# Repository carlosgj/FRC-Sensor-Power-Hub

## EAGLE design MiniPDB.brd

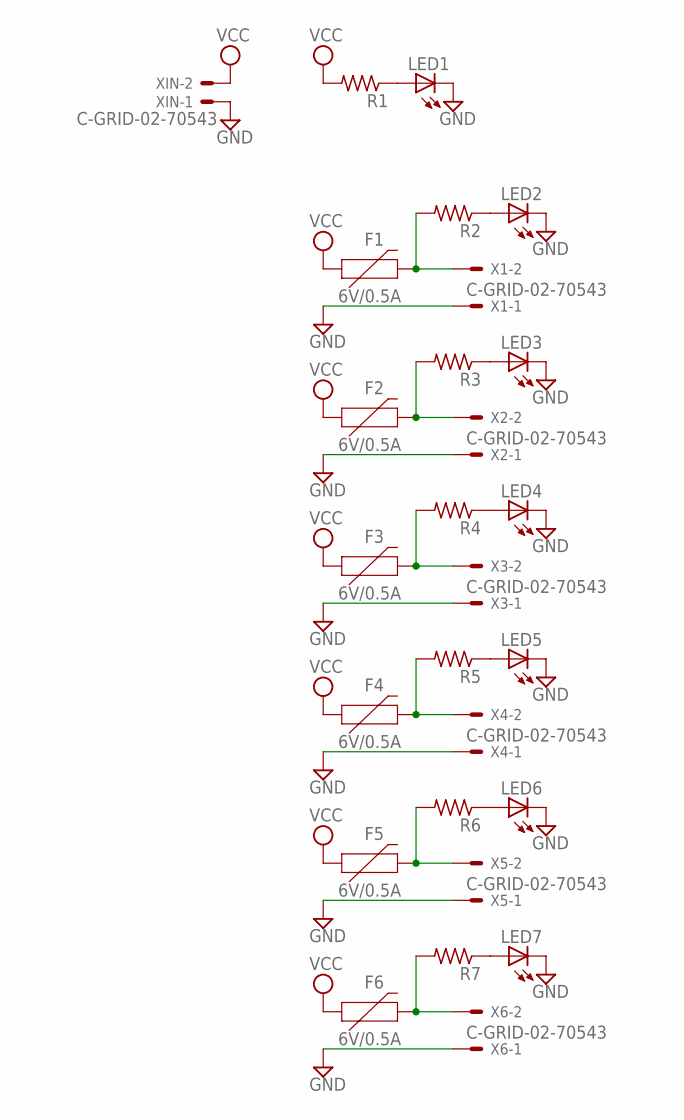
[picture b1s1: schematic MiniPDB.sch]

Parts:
F1, F2, F3, F4, F5, F6: 6V/0.5A; 1206
LED1, LED2, LED3, LED4, LED5, LED6, LED7: LEDCHIPLED_1206; CHIPLED_1206
R1, R2, R3, R4, R5, R6, R7: R-US_R1206; R1206
X1, X2, X3, X4, X5, X6: C-GRID-02-70543; 70543-02
XIN: C-GRID-02-70543; 70543-02

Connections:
GND: LED1.C, LED2.C, LED3.C, LED4.C, LED5.C, LED6.C, LED7.C, X1.1, X2.1, X3.1, X4.1, X5.1, X6.1, XIN.1
unnamed: F1.2, R2.2, X1.2
unnamed: LED2.A, R2.1
unnamed: LED1.A, R1.1
unnamed: F2.2, R3.2, X2.2
unnamed: LED3.A, R3.1
unnamed: F3.2, R4.2, X3.2
unnamed: LED4.A, R4.1
unnamed: F4.2, R5.2, X4.2
unnamed: LED5.A, R5.1
unnamed: F5.2, R6.2, X5.2
unnamed: LED6.A, R6.1
unnamed: F6.2, R7.2, X6.2
unnamed: LED7.A, R7.1
VCC: F1.1, F2.1, F3.1, F4.1, F5.1, F6.1, R1.2, XIN.2

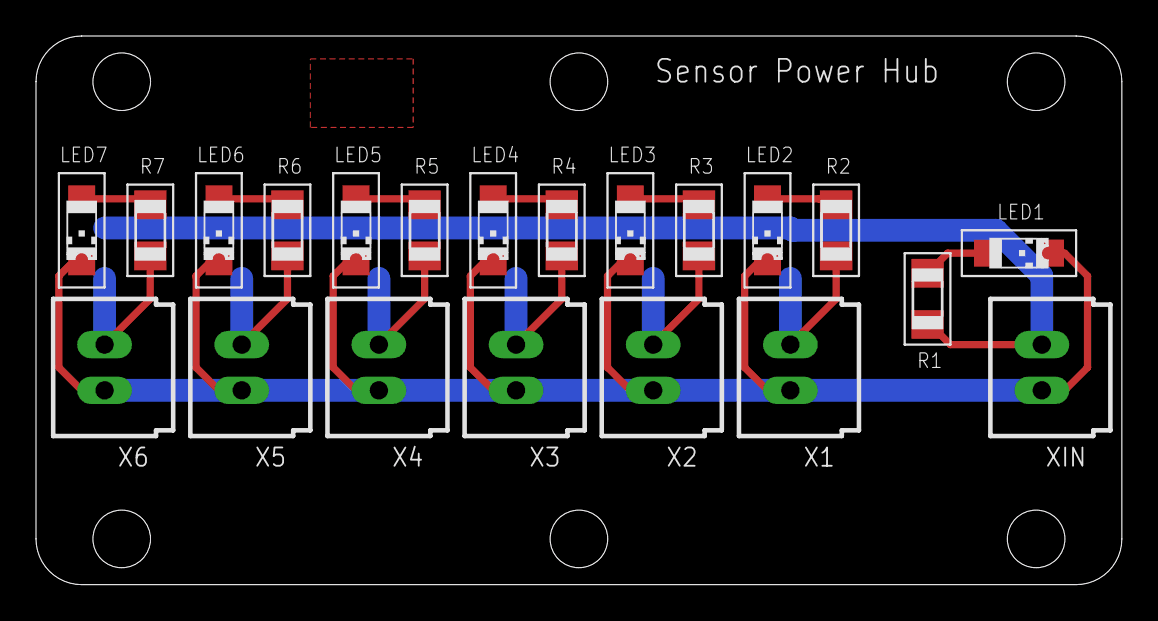
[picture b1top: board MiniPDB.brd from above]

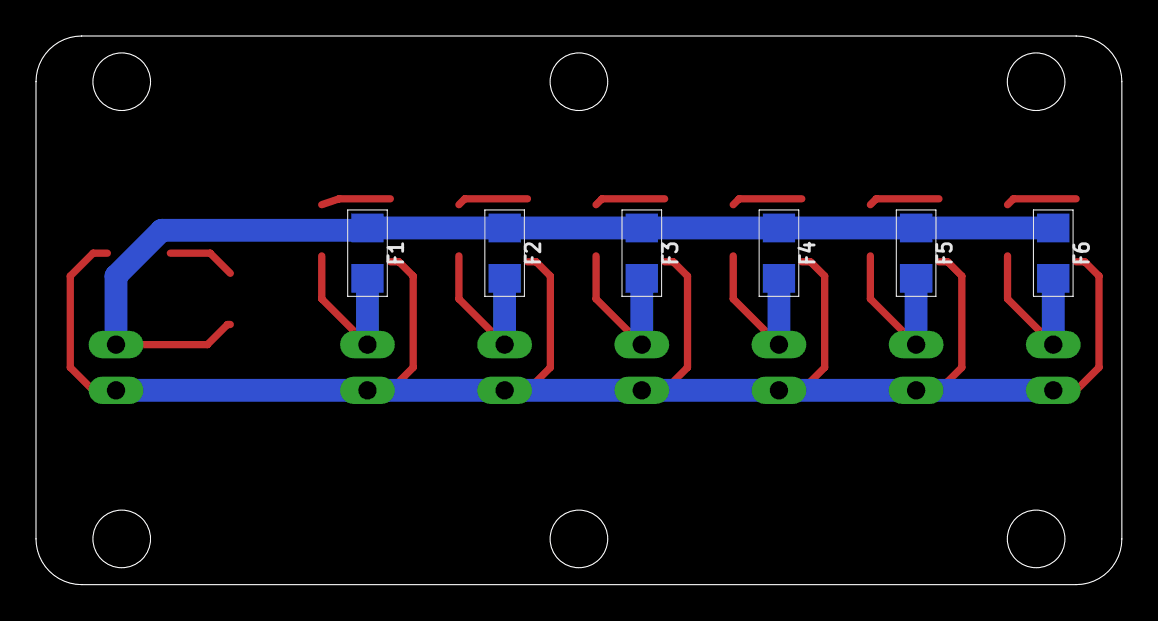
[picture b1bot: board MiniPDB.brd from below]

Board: 2 copper layers, 60.3 x 30.5 mm, 27 parts (6 on the bottom side), 15 nets.

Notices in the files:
parts and their libraries:
SparkFun-Fuses: Licensing: Creative Commons ShareAlike 4.0 International - https://creativecommons.org/licenses/by-sa/4.0
